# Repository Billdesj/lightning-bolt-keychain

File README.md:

# USB-C Lightning Bolt PCB Keychain

A USB-C powered light-up PCB keychain shaped like a chunky lightning bolt. Plug it into a USB-C charger, power bank, or powered port and the amber LEDs light the bolt.

## Design

- USB-C power-only input, 5 V VBUS
- Correct USB-C sink detection with 5.1k pull-downs on CC1 and CC2
- 500 mA resettable fuse footprint on VBUS
- Five amber 0603 LEDs arranged down the lightning bolt
- One 1k current-limit resistor per LED branch
- Matte black solder mask with ENIG finish recommended
- Reinforced plated keyring hole
- Flat bottom edge for the USB-C receptacle

## Electrical Design

```text
USB-C VBUS -> F1 polyfuse -> VLED
CC1 -> 5.1k -> GND
CC2 -> 5.1k -> GND
VLED -> 1k resistor -> amber LED -> GND  (five branches)
```

The board is intentionally power-only. It does not route USB data. The CC pull-down resistors are what make a USB-C source provide default 5 V to the board.

## Files

- `hardware/lightning-bolt-keychain.kicad_pro` - KiCad project file
- `hardware/lightning-bolt-keychain.kicad_sch` - USB-C powered schematic
- `hardware/lightning-bolt-keychain.kicad_pcb` - lightning-bolt PCB layout
- `bom/lightning-bolt-keychain-bom.csv` - parts list
- `fabrication/fab-notes.md` - PCB fab and assembly notes
- `fabrication/lightning-bolt-keychain-fab-package.zip` - Gerber, drill, BOM, and validation reports

## Build Notes

- Use a USB-C power-only receptacle matching the KiCad footprint, currently `GCT USB4125` family.
- Use 5.1k 0603 resistors for `RCC1` and `RCC2`; these are required for USB-C power input.
- Start with 1k LED resistors for gentle brightness from USB 5 V. Lower values such as 680 ohm are brighter; higher values such as 1.5k or 2.2k are softer.
- Confirm the USB-C connector orientation before ordering boards.

## Fab Readiness

- KiCad ERC: 0 violations
- KiCad DRC: 0 violations, 0 unconnected items
- Gerbers and drill files are exported under `fabrication/`
- Upload `fabrication/lightning-bolt-keychain-fab-package.zip` to a PCB fab for quoting

## Visual Direction

Recommended finish:

- PCB: matte black solder mask
- Copper finish: ENIG / gold
- LEDs: amber / warm yellow
- Thickness: 1.6 mm

Keep the bolt chunky. Thin points look cool in renders but keychains get abused.

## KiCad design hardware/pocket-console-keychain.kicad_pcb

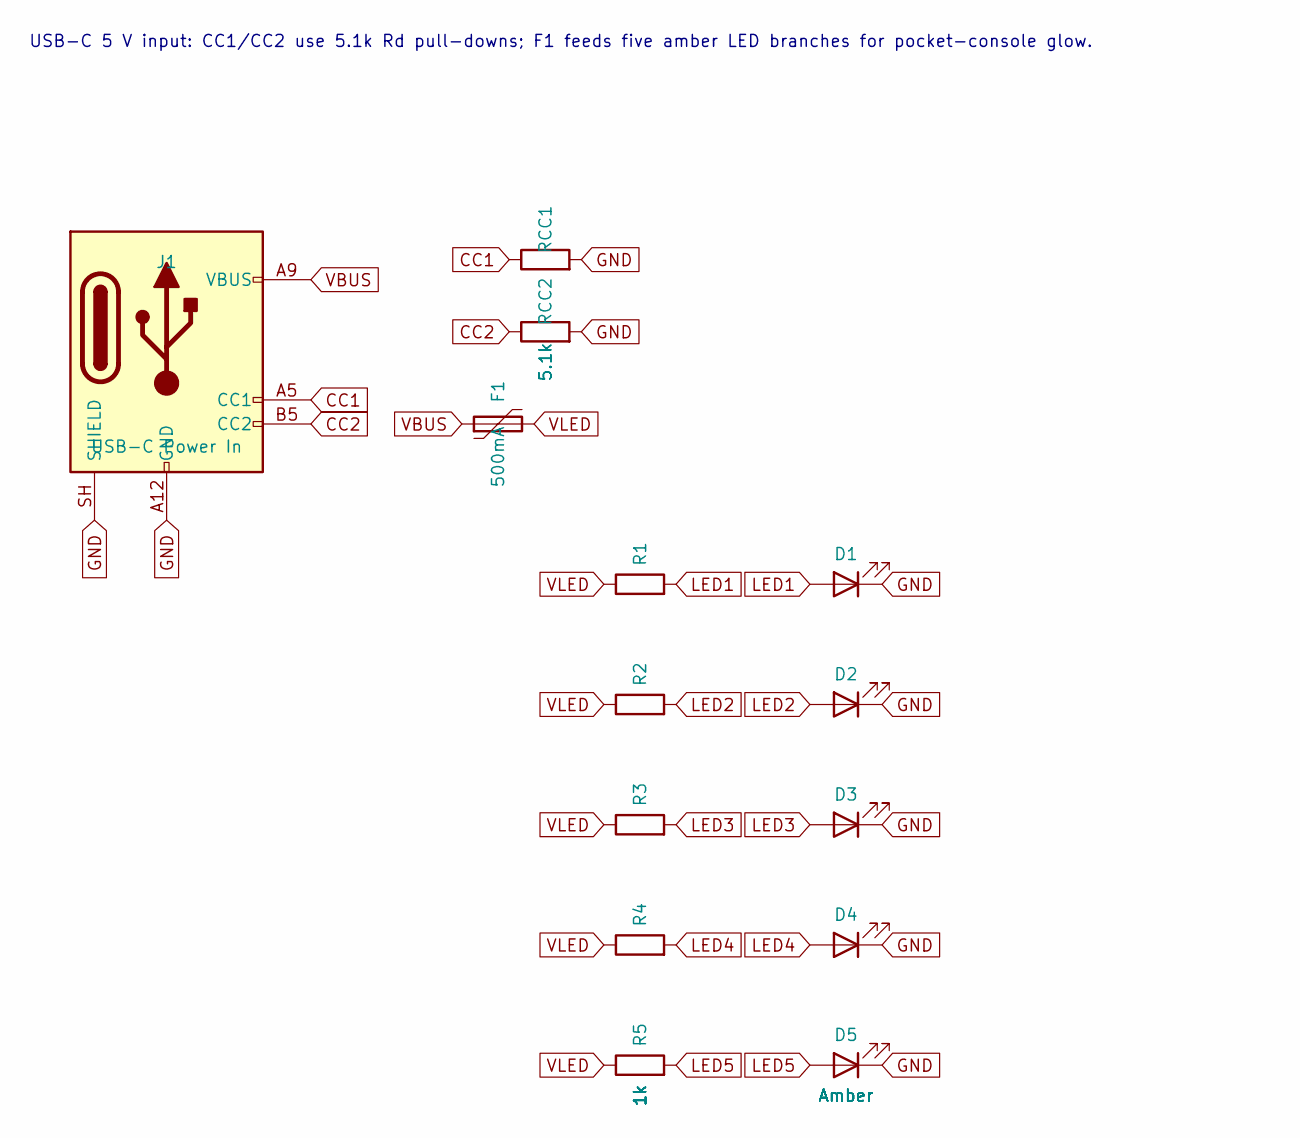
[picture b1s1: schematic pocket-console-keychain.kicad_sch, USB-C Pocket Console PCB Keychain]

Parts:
D1, D2, D3, D4, D5: Amber; LED_0603_1608Metric
F1: 500mA; Fuse_1206_3216Metric
J1: USB-C Power In; USB_C_Receptacle_GCT_USB4125-xx-x_6P_TopMnt_Horizontal
R1, R2, R3, R4, R5: 1k; R_0603_1608Metric
RCC1, RCC2: 5.1k; R_0603_1608Metric

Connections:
CC1: J1.A5 (CC1), RCC1.1
CC2: J1.B5 (CC2), RCC2.1
GND: D1.1 (K), D2.1 (K), D3.1 (K), D4.1 (K), D5.1 (K), J1.A12 (GND), J1.B12 (GND), J1.SH (SHIELD), RCC1.2, RCC2.2
LED1: D1.2 (A), R1.2
LED2: D2.2 (A), R2.2
LED3: D3.2 (A), R3.2
LED4: D4.2 (A), R4.2
LED5: D5.2 (A), R5.2
VBUS: F1.1, J1.A9 (VBUS), J1.B9 (VBUS)
VLED: F1.2, R1.1, R2.1, R3.1, R4.1, R5.1

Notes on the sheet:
USB-C 5 V input: CC1/CC2 use 5.1k Rd pull-downs; F1 feeds five amber LED branches for pocket-console glow.

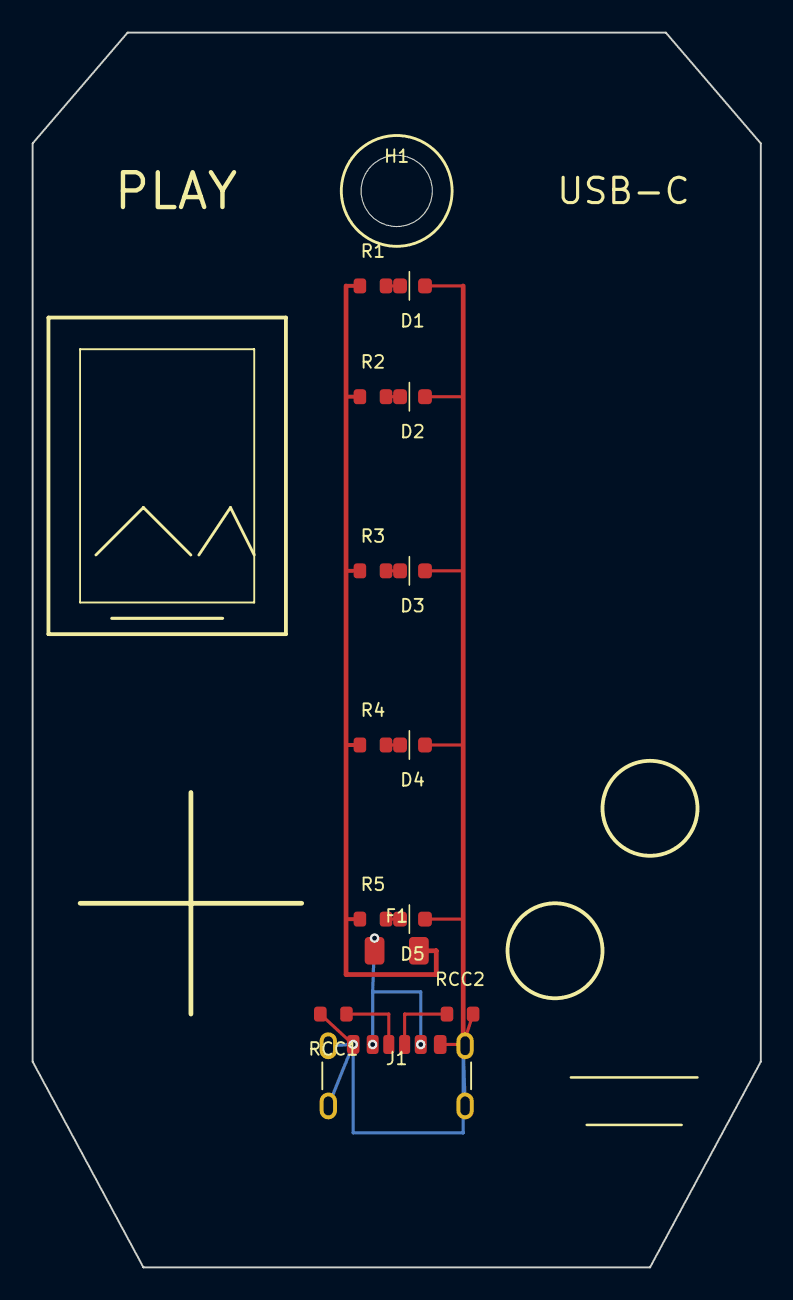
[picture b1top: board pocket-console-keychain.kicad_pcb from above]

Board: 2 copper layers, 46.0 x 78.0 mm, 15 parts (0 on the bottom side), 10 nets.

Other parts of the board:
H1: Keyring; MountingHole_4.3mm_M4_Pad_Via

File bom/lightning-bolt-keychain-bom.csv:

Designator,Quantity,Value,Description,Suggested Footprint,Notes
J1,1,USB-C,Power-only USB-C receptacle,Connector_USB:USB_C_Receptacle_GCT_USB4125-xx-x_6P_TopMnt_Horizontal,"Use GCT USB4125 family or verify equivalent footprint before ordering."
F1,1,500mA,Resettable polyfuse,Fuse:Fuse_1206_3216Metric,"USB VBUS input protection; choose hold current to suit desired brightness."
RCC1 RCC2,2,5.1k,USB-C CC pull-down resistor,Resistor_SMD:R_0603_1608Metric,"Required Rd resistors so USB-C sources enable default 5 V."
R1 R2 R3 R4 R5,5,1k,LED current-limit resistor,Resistor_SMD:R_0603_1608Metric,"Tune for brightness; 680 ohm brighter, 1.5k/2.2k softer."
D1 D2 D3 D4 D5,5,Amber LED,0603 amber LED,LED_SMD:LED_0603_1608Metric,"Low forward-voltage amber/warm yellow recommended."
H1,1,Keyring hole,Gold-plated reinforced keyring hole,MountingHole:MountingHole_4.3mm_M4_Pad_Via,"Use annular copper; avoid sharp metal keyring edges scraping solder mask."
PCB,1,USB-C lightning bolt PCB,1.6 mm FR4 PCB with ENIG finish,Custom,Matte black solder mask recommended
